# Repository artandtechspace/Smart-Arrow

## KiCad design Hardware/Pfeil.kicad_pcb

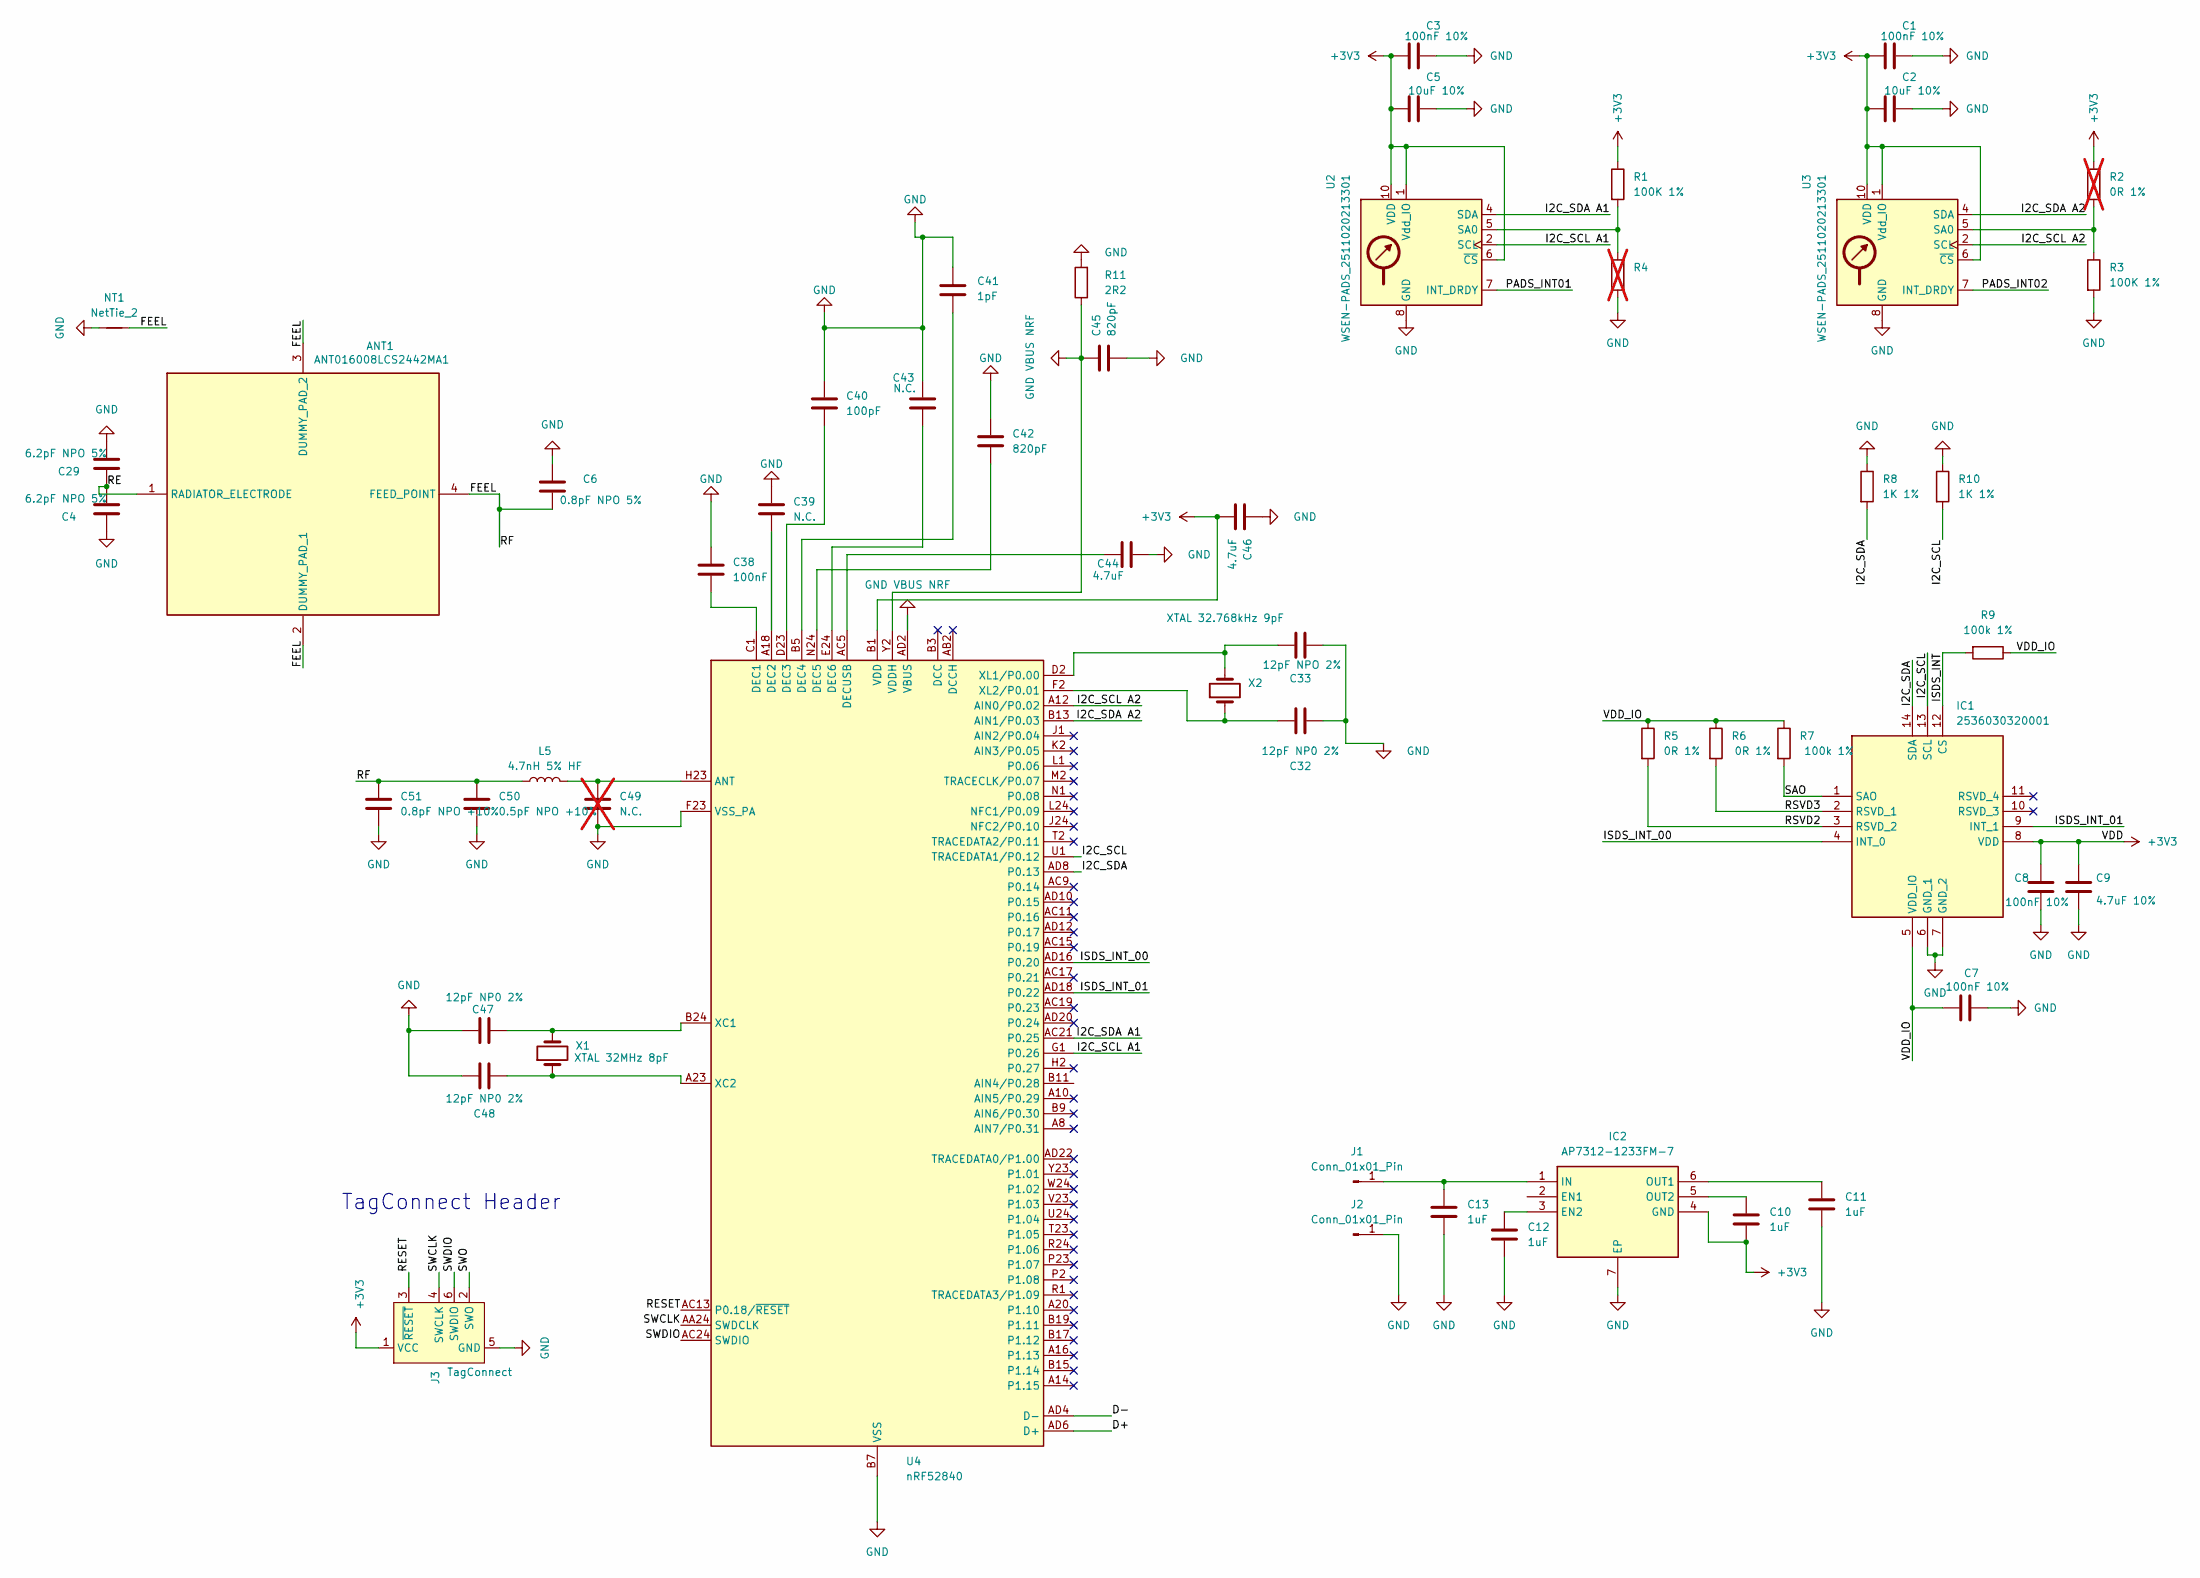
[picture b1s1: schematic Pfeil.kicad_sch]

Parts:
ANT1: ANT016008LCS2442MA1; Mouser Part Number 810-ANT168LCS2442MA1
C1, C3, C7, C8: 100nF 10%; C_0201_0603Metric
C2, C5: 10uF 10%; C_0402_1005Metric
C4, C29: 6.2pF NPO 5%; C_0201_0603Metric
C6: 0.8pF NPO 5%; C_0201_0603Metric
C9: 4.7uF 10%; C_0201_0603Metric
C10, C11, C12, C13: 1uF; C_0805_2012Metric
C32, C47, C48: 12pF NP0 2%; C_0201_0603Metric
C33: 12pF NPO 2%; C_0201_0603Metric
C38: 100nF; C_0201_0603Metric
C39, C43: N.C.; C_0201_0603Metric
C40: 100pF; C_0201_0603Metric
C41: 1pF; C_0201_0603Metric
C42, C45: 820pF; C_0201_0603Metric
C44, C46: 4.7uF; C_0201_0603Metric
C49: N.C.; C_0201_0603Metric; not fitted
C50: 0.5pF NPO +10%; C_0201_0603Metric
C51: 0.8pF NPO +10%; C_0201_0603Metric
IC1: 2536030320001; Mouser Part Number 710-2536030320001
IC2: AP7312-1233FM-7; SON50P201X181X60-7N; Mouser Part Number 621-AP7312-1233FM-7
J1, J2: Conn_01x01_Pin; SolderWirePad_1x01_SMD_1x2mm
J3: TagConnect; Tag-Connect_TC2030-IDC-NL_2x03_P1.27mm_Vertical
L5: 4.7nH 5% HF; LED_0402_1005Metric
NT1: NetTie_2; NetTie-2_SMD_Pad0.5mm
R1, R3: 100K 1%; R_0201_0603Metric
R2: 0R 1%; R_0201_0603Metric; not fitted
R4: R_0201_0603Metric; not fitted
R5, R6: 0R 1%; R_0201_0603Metric
R7, R9: 100k 1%; R_0201_0603Metric
R8, R10: 1K 1%; R_0201_0603Metric
R11: 2R2; R_0201_0603Metric
U2, U3: WSEN-PADS_2511020213301; ST_HLGA-10_2x2mm_P0.5mm_LayoutBorder3x2y
U4: nRF52840; Nordic_AQFN-73-1EP_7x7mm_P0.5mm
X1: XTAL 32MHz 8pF; Crystal_SMD_2016-4Pin_2.0x1.6mm
X2: XTAL 32.768kHz 9pF; Crystal_SMD_2016-4Pin_2.0x1.6mm

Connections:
+3V3: C1.1, C2.1, C3.1, C5.1, C8.1, C9.1, C10.2, C46.2, IC1.8 (VDD), IC2.4 (GND), J3.1 (VCC), R1.1, R2.1, U2.1 (Vdd_IO), U2.6 (~CS), U2.10 (VDD), U3.1 (Vdd_IO), U3.6 (~CS), U3.10 (VDD), U4.A22 (VDD), U4.AD14 (VDD), U4.AD23 (VDD), U4.B1 (VDD), U4.W1 (VDD)
/D+: U4.AD6 (D+)
/D-: U4.AD4 (D-)
/FEEL: ANT1.2 (DUMMY_PAD_1), ANT1.3 (DUMMY_PAD_2), ANT1.4 (FEED_POINT), C6.2, C50.1, C51.1, L5.1, NT1.2
/I2C_SCL: IC1.13 (SCL), R10.2, U4.U1 (TRACEDATA1/P0.12)
/I2C_SCL A1: U2.2 (SCL), U4.G1 (P0.26)
/I2C_SCL A2: U3.2 (SCL), U4.A12 (AIN0/P0.02)
/I2C_SDA: IC1.14 (SDA), R8.2, U4.AD8 (P0.13)
/I2C_SDA A1: U2.4 (SDA), U4.AC21 (P0.25)
/I2C_SDA A2: U3.4 (SDA), U4.B13 (AIN1/P0.03)
/ISDS_INT: IC1.12 (CS), R9.2
/ISDS_INT_00: IC1.4 (INT_0), U4.AD16 (P0.20)
/ISDS_INT_01: IC1.9 (INT_1), U4.AD18 (P0.22)
/PADS_INT01: U2.7 (INT_DRDY)
/PADS_INT02: U3.7 (INT_DRDY)
/RE: ANT1.1 (RADIATOR_ELECTRODE), C4.2, C29.1
/RESET: J3.3 (~RESET), U4.AC13 (P0.18/~RESET)
/RSVD2: IC1.3 (RSVD_2), R5.2
/RSVD3: IC1.2 (RSVD_1), R6.2
/SAO: IC1.1 (SAO), R7.2
/SWCLK: J3.4 (SWCLK), U4.AA24 (SWDCLK)
/SWDIO: J3.6 (SWDIO), U4.AC24 (SWDIO)
/SWO: J3.2 (SWO)
/VDD_IO: C7.1, IC1.5 (VDD_IO), R5.1, R6.1, R7.1, R9.1
GND: C1.2, C2.2, C3.2, C4.1, C5.2, C6.1, C7.2, C8.2, C9.2, C11.2, C12.2, C13.2, C29.2, C32.2, C33.1, C38.1, C39.1, C40.1, C41.1, C42.1, C43.2, C44.1, C45.2, C46.1, C47.2, C48.2, C49.2, C50.2, C51.2, IC1.6 (GND_1), IC1.7 (GND_2), IC2.7 (EP), J2.1, J3.5 (GND), NT1.1, R3.2, R4.2, R8.1, R10.1, R11.2, U2.3 (GND), U2.8 (GND), U2.9 (GND), U3.3 (GND), U3.8 (GND), U3.9 (GND), U4.B7 (VSS), U4.EP (VSS), U4.F23 (VSS_PA)
GND VBUS NRF: C45.1, R11.1, U4.AD2 (VBUS), U4.Y2 (VDDH)
unnamed: C12.1, IC2.3 (EN2)
unnamed: C13.1, IC2.1 (IN), J1.1
unnamed: C11.1, IC2.6 (OUT1)
unnamed: C10.1, IC2.5 (OUT2)
unnamed: R1.2, R4.1, U2.5 (SA0)
unnamed: R2.2, R3.1, U3.5 (SA0)
unnamed: C49.1, L5.2, U4.H23 (ANT)
unnamed: C38.2, U4.C1 (DEC1)
unnamed: C39.2, U4.A18 (DEC2)
unnamed: C40.2, U4.D23 (DEC3)
unnamed: C41.2, U4.B5 (DEC4)
unnamed: C42.2, U4.N24 (DEC5)
unnamed: C43.1, U4.E24 (DEC6)
unnamed: C44.2, U4.AC5 (DECUSB)
unnamed: C47.1, U4.B24 (XC1), X1.2
unnamed: C48.1, U4.A23 (XC2), X1.1
unnamed: C33.2, U4.D2 (XL1/P0.00), X2.2
unnamed: C32.1, U4.F2 (XL2/P0.01), X2.1

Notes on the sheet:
TagConnect Header

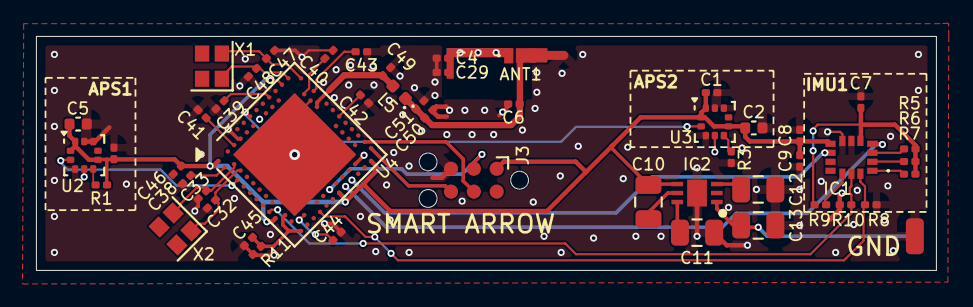
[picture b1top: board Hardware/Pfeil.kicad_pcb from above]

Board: 4 copper layers, 50.0 x 13.0 mm, 52 parts (1 on the bottom side), 39 nets.

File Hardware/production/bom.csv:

Designator,Footprint,Quantity,Value,LCSC Part #
ANT1,ANT016008LCS2442MA1,1,ANT016008LCS2442MA1,
"C1, C3, C7, C8",0201,4,100nF 10%,
"C10, C11, C12, C13",0805,4,1uF,
"C2, C5",0402,2,10uF 10%,
"C29, C4",0201,2,6.2pF NPO 5%,
"C32, C47, C48",0201,3,12pF NP0 2%,
C33,0201,1,12pF NPO 2%,
C38,0201,1,100nF,
"C39, C43",0201,2,N.C.,
C40,0201,1,100pF,
C41,0201,1,1pF,
"C42, C45",0201,2,820pF,
"C44, C46",0201,2,4.7uF,
C50,0201,1,0.5pF NPO +10%,
C51,0201,1,0.8pF NPO +10%,
C6,0201,1,0.8pF NPO 5%,
C9,0201,1,4.7uF 10%,
IC1,2536030320001,1,2536030320001,
IC2,SON50P201X181X60-7N,1,AP7312-1233FM-7,
"J1, J2",SolderWirePad_1x01_SMD_1x2mm,2,Conn_01x01_Pin,
L5,0402,1,4.7nH 5% HF,
"R1, R3, R7, R9",0201,4,100K 1%,
"R10, R8",0201,2,1K 1%,
R11,0201,1,2R2,
"R5, R6",0201,2,0R 1%,
"U2, U3",ST_HLGA-10_2x2mm_P0.5mm_LayoutBorder3x2y,2,WSEN-PADS_2511020213301,
U4,Nordic_AQFN-73-1EP_7x7mm_P0.5mm,1,nRF52840,
X1,Crystal_SMD_2016-4Pin_2.0x1.6mm,1,XTAL 32MHz 8pF,
X2,Crystal_SMD_2016-4Pin_2.0x1.6mm,1,XTAL 32.768kHz 9pF,

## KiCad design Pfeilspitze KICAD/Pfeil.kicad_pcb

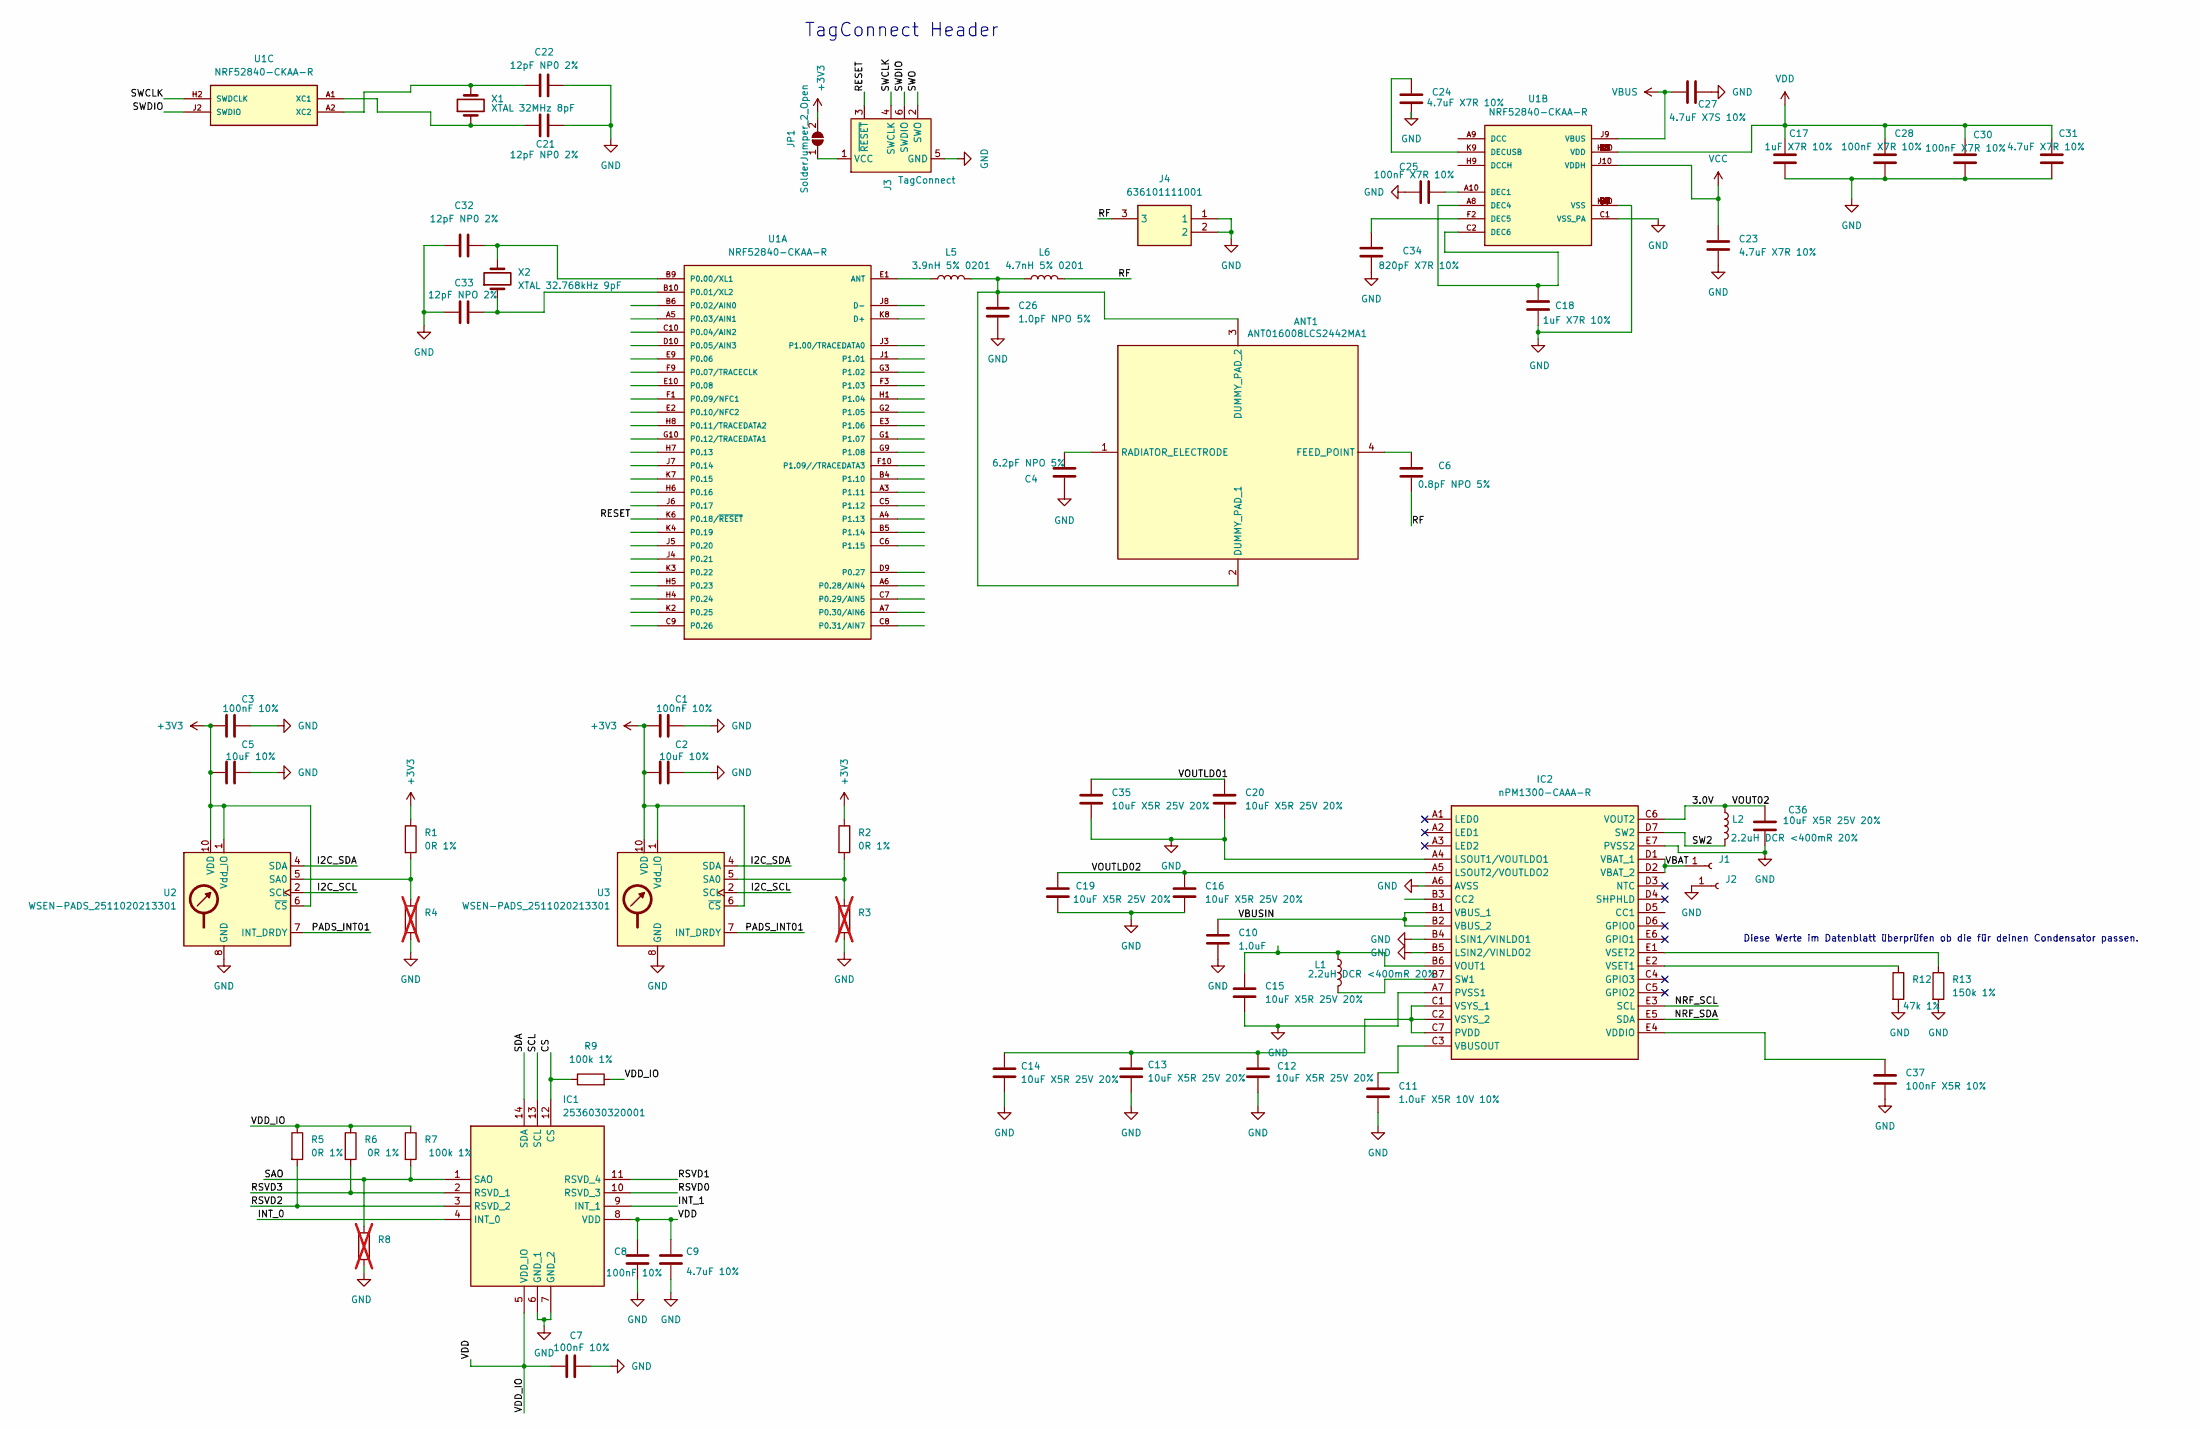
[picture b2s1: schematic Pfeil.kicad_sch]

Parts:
ANT1: ANT016008LCS2442MA1; Mouser Part Number 810-ANT168LCS2442MA1
C1, C3, C7, C8: 100nF 10%; C_0201_0603Metric
C2, C5: 10uF 10%; C_0201_0603Metric
C4: 6.2pF NPO 5%; C_0201_0603Metric
C6: 0.8pF NPO 5%; C_0201_0603Metric
C9: 4.7uF 10%; C_0201_0603Metric
C10: 1.0uF; C_0201_0603Metric
C11: 1.0uF X5R 10V 10%; C_0201_0603Metric
C12, C13, C14, C15, C16, C19, C20, C35, C36: 10uF X5R 25V 20%; C_0201_0603Metric
C17, C18: 1uF X7R 10%; C_0201_0603Metric
C21, C22, C32: 12pF NP0 2%; C_0201_0603Metric
C23, C24, C31: 4.7uF X7R 10%; C_0201_0603Metric
C25, C28, C30: 100nF X7R 10%; C_0201_0603Metric
C26: 1.0pF NPO 5%; C_0201_0603Metric
C27: 4.7uF X7S 10%; C_0201_0603Metric
C33: 12pF NPO 2%; C_0201_0603Metric
C34: 820pF X7R 10%; C_0201_0603Metric
C37: 100nF X5R 10%; C_0201_0603Metric
IC1: 2536030320001; Mouser Part Number 710-2536030320001
IC2: nPM1300-CAAA-R; BGA35C44P7X5_308X238X51; Mouser Part Number 949-NPM1300-CAAA-R
J1, J2: Conn_01x01_Socket; TestPoint_Pad_2.5x2.5mm
J3: TagConnect; Tag-Connect_TC2030-IDC-NL_2x03_P1.27mm_Vertical
J4: 636101111001; Mouser Part Number 710-636101111001
JP1: SolderJumper_2_Open; SolderJumper-2_P1.3mm_Open_Pad1.0x1.5mm
L1, L2: 2.2uH DCR <400mR 20%; L_Coilcraft_XAL7020-152
L5: 3.9nH 5% 0201; L_Coilcraft_XAL7020-152
L6: 4.7nH 5% 0201; L_Coilcraft_XAL7020-152
R1, R2, R5, R6: 0R 1%; R_0201_0603Metric
R3, R4, R8: R_0201_0603Metric; not fitted
R7, R9: 100k 1%; R_0201_0603Metric
R12: 47k 1%; R_0201_0603Metric
R13: 150k 1%; R_0201_0603Metric
U1: NRF52840-CKAA-R; BGA94C35P10X10_360X354X51N; PARTREV 1.1
U2, U3: WSEN-PADS_2511020213301; ST_HLGA-10_2x2mm_P0.5mm_LayoutBorder3x2y
X1: XTAL 32MHz 8pF; Crystal_SMD_2016-4Pin_2.0x1.6mm
X2: XTAL 32.768kHz 9pF; Crystal_SMD_2012-2Pin_2.0x1.2mm

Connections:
+3V3: C1.1, C2.1, C3.1, C5.1, JP1.2 (B), R1.1, R2.1, U2.1 (Vdd_IO), U2.6 (~CS), U2.10 (VDD), U3.1 (Vdd_IO), U3.6 (~CS), U3.10 (VDD)
/3.0V: C36.1, IC2.C6 (VOUT2), L2.1
/CS: IC1.12 (CS), R9.1
/I2C_SCL: U2.2 (SCL), U3.2 (SCL)
/I2C_SDA: U2.4 (SDA), U3.4 (SDA)
/INT_0: IC1.4 (INT_0)
/INT_1: IC1.9 (INT_1)
/NRF_SCL: IC2.E3 (SCL)
/NRF_SDA: IC2.E5 (SDA)
/PADS_INT01: U2.7 (INT_DRDY), U3.7 (INT_DRDY)
/RESET: J3.3 (~RESET), U1.K6 (P0.18/~RESET)
/RF: C6.2, J4.3, L6.2
/RSVD0: IC1.10 (RSVD_3)
/RSVD1: IC1.11 (RSVD_4)
/RSVD2: IC1.3 (RSVD_2), R5.2
/RSVD3: IC1.2 (RSVD_1), R6.2
/SAO: IC1.1 (SAO), R7.2, R8.1
/SCL: IC1.13 (SCL)
/SDA: IC1.14 (SDA)
/SW2: IC2.D7 (SW2), L2.2
/SWCLK: J3.4 (SWCLK), U1.H2 (SWDCLK)
/SWDIO: J3.6 (SWDIO), U1.J2 (SWDIO)
/SWO: J3.2 (SWO)
/VBAT: IC2.D1 (VBAT_1), IC2.D2 (VBAT_2), J1.1
/VBUSIN: C10.1, IC2.B1 (VBUS_1), IC2.B2 (VBUS_2)
/VOUTLD01: C20.1, C35.1
/VOUTLD02: C16.1, C19.1, IC2.A5 (LSOUT2/VOUTLDO2)
GND: C1.2, C2.2, C3.2, C4.1, C5.2, C7.2, C8.2, C9.2, C10.2, C11.2, C12.2, C13.2, C14.2, C15.2, C16.2, C17.1, C18.1, C19.2, C20.2, C21.2, C22.2, C23.2, C24.2, C25.1, C26.2, C27.2, C28.1, C30.1, C31.1, C32.2, C33.1, C34.2, C35.2, C36.2, C37.2, IC1.6 (GND_1), IC1.7 (GND_2), IC2.A4 (LSOUT1/VOUTLDO1), IC2.A6 (AVSS), IC2.A7 (PVSS1), IC2.B4 (LSIN1/VINLDO1), IC2.B5 (LSIN2/VINLDO2), IC2.E7 (PVSS2), J2.1, J3.5 (GND), J4.1, J4.2, R3.2, R4.2, R8.2, R12.2, R13.2, U1.B7 (VSS), U1.C1 (VSS_PA), U1.C4 (VSS), U1.D3 (VSS), U1.D4 (VSS), U1.D5 (VSS), U1.D6 (VSS), U1.D7 (VSS), U1.D8 (VSS), U1.E4 (VSS), U1.E5 (VSS), U1.E6 (VSS), U1.E7 (VSS), U1.E8 (VSS), U1.F4 (VSS), U1.F5 (VSS), U1.F6 (VSS), U1.F7 (VSS), U1.F8 (VSS), U1.G4 (VSS), U1.G5 (VSS), U1.G6 (VSS), U1.G7 (VSS), U1.G8 (VSS), U1.K10 (VSS), U2.3 (GND), U2.8 (GND), U2.9 (GND), U3.3 (GND), U3.8 (GND), U3.9 (GND)
unnamed: ANT1.2 (DUMMY_PAD_1), ANT1.3 (DUMMY_PAD_2), C26.1, L5.2, L6.1
unnamed: ANT1.4 (FEED_POINT), C6.1
unnamed: ANT1.1 (RADIATOR_ELECTRODE), C4.2
unnamed: C12.1, C13.1, C14.1, IC2.C1 (VSYS_1), IC2.C2 (VSYS_2), IC2.C7 (PVDD)
unnamed: IC2.B7 (SW1), L1.2
unnamed: C11.1, IC2.C3 (VBUSOUT)
unnamed: C37.1, IC2.E4 (VDDIO)
unnamed: C15.1, IC2.B6 (VOUT1), L1.1
unnamed: IC2.E2 (VSET1), R12.1
unnamed: IC2.E1 (VSET2), R13.1
unnamed: J3.1 (VCC), JP1.1 (A)
unnamed: L5.1, U1.E1 (ANT)
unnamed: C32.1, U1.B9 (P0.00/XL1), X2.2
unnamed: C33.2, U1.B10 (P0.01/XL2), X2.1
unnamed: C25.2, U1.A10 (DEC1)
unnamed: C18.2, U1.A8 (DEC4), U1.C2 (DEC6)
unnamed: C34.1, U1.F2 (DEC5)
unnamed: C24.1, U1.K9 (DECUSB)
unnamed: C21.1, U1.A1 (XC1), X1.1
unnamed: C22.1, U1.A2 (XC2), X1.2
unnamed: R1.2, R4.1, U2.5 (SA0)
unnamed: R2.2, R3.1, U3.5 (SA0)
VBUS: C27.1, U1.J9 (VBUS)
VCC: C23.1, U1.J10 (VDDH)
VDD: C7.1, C8.1, C9.1, C17.2, C28.2, C30.2, C31.2, IC1.5 (VDD_IO), IC1.8 (VDD), R5.1, R6.1, R7.1, R9.2, U1.B3 (VDD), U1.B8 (VDD), U1.H10 (VDD), U1.K1 (VDD), U1.K5 (VDD)

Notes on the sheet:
Diese Werte im Datenblatt überprüfen ob die für deinen Condensator passen.
TagConnect Header

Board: 2 copper layers, 64 parts (25 on the bottom side), 44 nets, no tracks yet.

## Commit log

2024-12-20 File Upload
2025-01-07 continued pcb routing
2025-01-08 table of content for Jufo 2025
2025-01-08 stl datas for the arrowhead
2025-01-17 first changes
2025-01-17 bezeichner update
2025-01-17 update docx
2025-01-17 backups
2025-01-25 error correction
2025-02-08 larger pcb
2025-02-08 Fix some shit
2025-02-09 reroute all
2025-02-09 fix some issues in scematic
2025-02-09 fixes
2025-02-09 Auf Süüüüüß Puschen
2025-02-10 Upload Softwar Example
2025-02-11 fixing and routing
2025-02-11 new gnd for ant
2025-02-13 new microcontroller ( other package in libs)
2025-02-14 nrf 52840 changing of the package
2025-02-14 bigger pcb and no more npm1300
2025-02-15 start ing to routing with the new pcb
2025-02-16 Routing and evry component is on the front
2025-02-18 Luca Berthold review
2025-02-18 Fix all sikscreen erros
2025-02-19 Bestellte version
2025-02-20 change via size
2025-02-20 final
2025-02-22 update last
2025-03-06 stl data
2025-03-06 test
2025-03-22 fixing
